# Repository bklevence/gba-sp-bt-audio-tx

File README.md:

GBA SP Bluetooth Audio Transmitter
===========

Parts needed
-------------------
* GBA SP plug/audio cable sourced from: ([GBA SP Audio Adapter](https://en.wikipedia.org/wiki/Game_Boy_Advance_SP#/media/File:Nintendo-Game-Boy-Advance-Headphone-Adapter.jpg))
* GBA Link Plug, need to de-solder from one of the following: ([Link Cable](https://en.m.wikipedia.org/wiki/GameCube_%E2%80%93_Game_Boy_Advance_link_cable) | [Wireless Adapter](https://en.m.wikipedia.org/wiki/Game_Boy_Advance_Wireless_Adapter))
* DIY bt audio module: ([4.1 BT Transmitter Module, KCX_BT_EMITTER 5V](https://www.aliexpress.com/item/33058710334.html?spm=a2g0s.9042311.0.0.52ea4c4dOgsJLK) | [Need to find Aipods compatible version](about:blank))
* PCB made diy or eventually osh park...

Find the cheapest plug you can via GBA-GB link cable, I have not tried taking apart a link cable to scavenge those plugs, I am not sure if they will have PCB through hole pins. Using Wireless Adapters can get expensive unless you want to use the larger case!

You can find tons of SP audio cables on eBay for cheap.

Repository Contents
-------------------
* **/Eagle Files** - Eagle Project, board and schematic

Links/Sources
-------------------
* [/r/Gameboy](https://www.reddit.com/r/Gameboy/)
* [Gameboy Advance Headphone Jack Mods](https://github.com/rorosaurus/gba-sp-headphone-jack)
* [/u/mmaxeator's intermal bt mod](https://web.archive.org/web/20201025163111/https://mmax.tech/?p=3895&lang=en)
* [Newer internal, need to find better adapter like this](https://www.reddit.com/r/Gameboy/comments/pwfgdh/update_ags001_unhinged_sp_bluetooth_mod_for/)
* [something like this may work](https://www.aliexpress.com/item/1005001764137150.html?spm=a2g0o.productlist.0.0.45955e42yAVyGd&algo_pvid=224b6ea4-3445-40f3-a414-e6287c7ee70a&algo_exp_id=224b6ea4-3445-40f3-a414-e6287c7ee70a-1&pdp_ext_f=%7B%22sku_id%22%3A%2212000017705120581%22%7D&pdp_pi=-1%3B29.99%3B-1%3B-1%40salePrice%3BUSD%3Bsearch-mainSearch)

toDo
-------------------
* better traces for mill for bt_tx pcb
* find bt_tx that works with airpods
* fit whole circuit in GBA wireless adapter?
* 3D model casing for circuit?

brief history
-------------------
There have been many posts on reddit of people doing similar stuff, I'm just trying to compile what I've learned contacting others and seeing what people are doing in the modding community.

people
-------------------
* bk brandonklevence@gmail.com

License Information
-------------------
The hardware is released under [Creative Commons Share-alike 3.0](http://creativecommons.org/licenses/by-sa/3.0/).
All other code is open source hardware so please feel free to do anything you want with it;
you buy me a beer if you use this and we meet someday ([Beerware license](http://en.wikipedia.org/wiki/Beerware)).

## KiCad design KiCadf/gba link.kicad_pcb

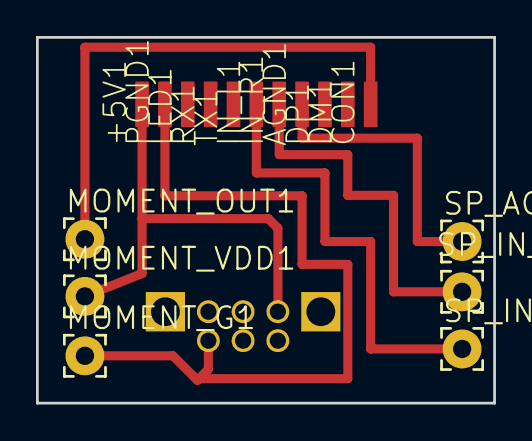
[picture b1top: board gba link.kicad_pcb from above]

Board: 2 copper layers, 25.4 x 20.3 mm, 18 parts (0 on the bottom side), 6 nets.

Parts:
+5V1: SMD2; SMD1,27-2,54
AGND1: SMD2; SMD1,27-2,54
CON1: SMD2; SMD1,27-2,54
DM1: SMD2; SMD1,27-2,54
DP1: SMD2; SMD1,27-2,54
IN_L1: SMD2; SMD1,27-2,54
IN_R1: SMD2; SMD1,27-2,54
LED1: SMD2; SMD1,27-2,54
MOMENT_G1: 2,15_1,0
MOMENT_OUT1: 2,15_1,0
MOMENT_VDD1: 2,15_1,0
PGND1: SMD2; SMD1,27-2,54
RX1: SMD2; SMD1,27-2,54
SP_AGND1: 2,15_1,0
SP_IN_L1: 2,15_1,0
SP_IN_R1: 2,15_1,0
TX1: SMD2; SMD1,27-2,54
U$1: GBA-LINKA; GBA-LINK-ALT

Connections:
unnamed: +5V1.1, MOMENT_VDD1.1, U$1.VCC
unnamed: AGND1.1, SP_AGND1.1
unnamed: CON1.1, MOMENT_OUT1.1
unnamed: IN_L1.1, SP_IN_L1.1
unnamed: IN_R1.1, SP_IN_R1.1
unnamed: MOMENT_G1.1, PGND1.1, U$1.GND

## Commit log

2020-10-25 Eagle Files
2020-10-28 KiCad Start
2020-11-22 schematicmarkup.jpeg
